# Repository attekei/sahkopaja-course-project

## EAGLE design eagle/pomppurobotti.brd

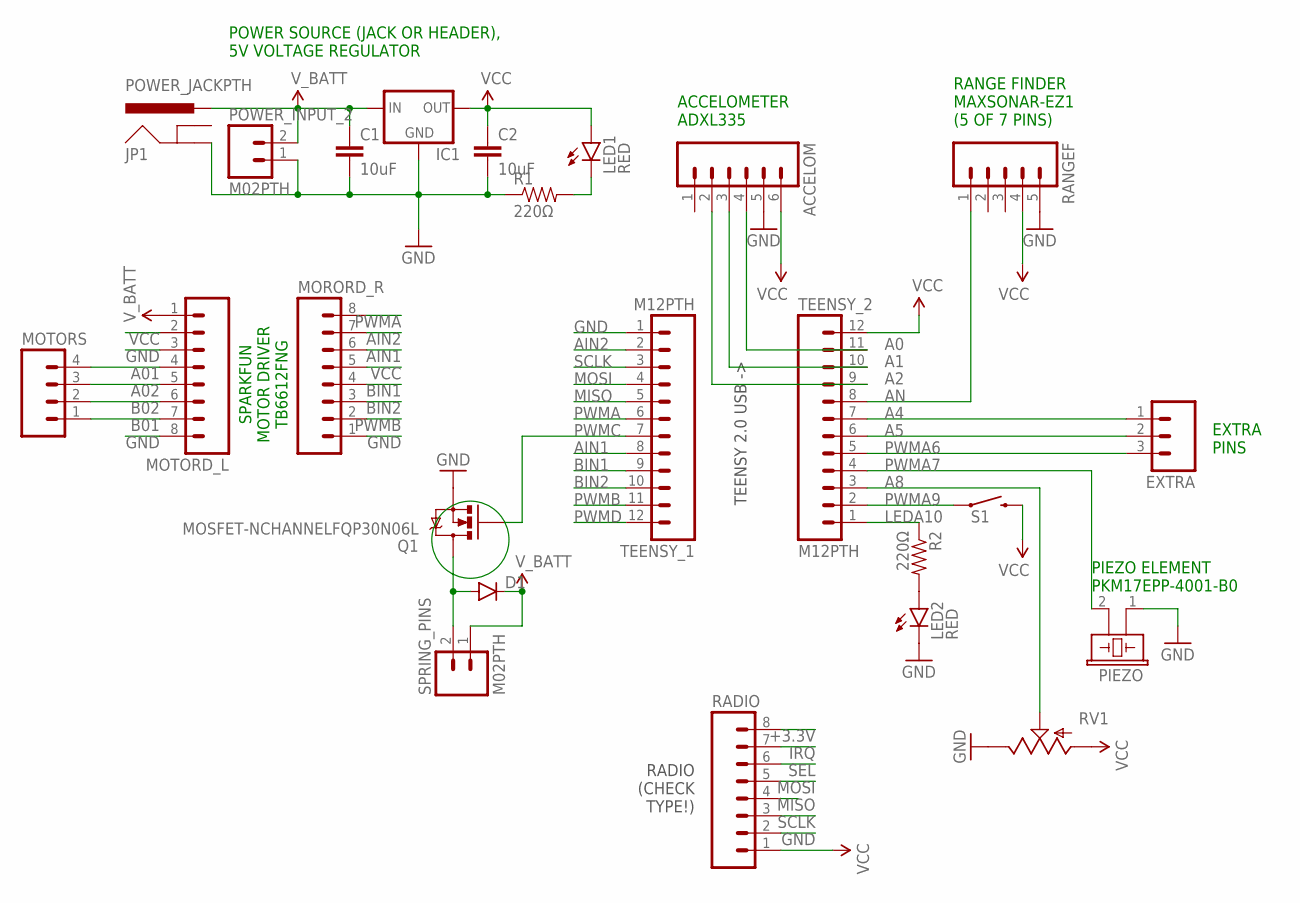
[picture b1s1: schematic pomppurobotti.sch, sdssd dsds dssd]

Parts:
ACCELOM: M06SILK_FEMALE_PTH; 1X06
C1, C2: 10uF; CAP-PTH-SMALL
D1: DIODEPTH; DIODE-1N4001
EXTRA: M03PTH; 1X03
IC1: V_REG_78XX-TO-220; TO-220-ALT
JP1: POWER_JACKPTH; POWER_JACK_PTH
LED1, LED2: RED; LED5MM
MORORD_R: M08LONGPADS; 1X08_LONGPADS
MOTORD_L: M08LONGPADS; 1X08_LONGPADS
MOTORS: M04PTH; 1X04
PIEZO: EFBAA40D101
POWER_INPUT_2: M02PTH; 1X02
Q1: MOSFET-NCHANNELFQP30N06L; TO220V
R1, R2: 220Ω; AXIAL-0.3
RADIO: M08; 1X08_ROUND
RANGEF: M05PTH; 1X05
RV1: POTTRIM; TRIM_POT
S1: SWITCH-MOMENTARY-2PTH; TACTILE-PTH
SPRING_PINS: M02PTH; 1X02
TEENSY_1, TEENSY_2: M12PTH; 1X12

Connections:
+3.3V: RADIO.8
A0: ACCELOM.2, TEENSY_2.9
A1: ACCELOM.3, TEENSY_2.10
A01: MOTORD_L.4, MOTORS.4
A2: ACCELOM.4, TEENSY_2.11
A02: MOTORD_L.5, MOTORS.3
A4: EXTRA.1, TEENSY_2.7
A5: EXTRA.2, TEENSY_2.6
A8: RV1.1 (S), TEENSY_2.3
AIN1: MORORD_R.6, TEENSY_1.8
AIN2: MORORD_R.7, TEENSY_1.2
AN: RANGEF.1, TEENSY_2.8
B01: MOTORD_L.7, MOTORS.1
B02: MOTORD_L.6, MOTORS.2
BIN1: MORORD_R.4, TEENSY_1.9
BIN2: MORORD_R.3, TEENSY_1.10
GND: ACCELOM.5, C1.2, C2.2, IC1.GND, JP1.GND, LED2.K (C), MORORD_R.1, MOTORD_L.3, MOTORD_L.8, PIEZO.1, POWER_INPUT_2.1, Q1.3 (S), R1.P$1 (1), RADIO.2, RANGEF.5, RV1.2 (E), TEENSY_1.1
IRQ: RADIO.7
LEDA10: R2.P$1 (1), TEENSY_2.1
MISO: RADIO.4, TEENSY_1.5
MOSI: RADIO.5, TEENSY_1.4
unnamed: LED1.K (C), R1.P$2 (2)
unnamed: LED2.A, R2.P$2 (2)
unnamed: D1.A, Q1.2 (D), SPRING_PINS.2
PWMA: MORORD_R.8, TEENSY_1.6
PWMA6: EXTRA.3, TEENSY_2.5
PWMA7: PIEZO.2, TEENSY_2.4
PWMA9: S1.1, TEENSY_2.2
PWMB: MORORD_R.2, TEENSY_1.11
PWMC: Q1.1 (G), TEENSY_1.7
PWMD: TEENSY_1.12
SCLK: RADIO.3, TEENSY_1.3
SEL: RADIO.6
VCC: ACCELOM.6, C2.1, IC1.OUT, LED1.A, MORORD_R.5, MOTORD_L.2, RADIO.1, RANGEF.4, RV1.3 (A), S1.3 (2), TEENSY_2.12
V_BATT: C1.1, D1.C, IC1.IN, JP1.PWR, MOTORD_L.1, POWER_INPUT_2.2, SPRING_PINS.1

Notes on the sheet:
TEENSY 2.0 USB ->
RADIO (CHECK TYPE!)
SPARKFUN MOTOR DRIVER TB6612FNG
ACCELOMETER ADXL335
POWER SOURCE (JACK OR HEADER), 5V VOLTAGE REGULATOR
PIEZO ELEMENT PKM17EPP-4001-B0
RANGE FINDER MAXSONAR-EZ1 (5 OF 7 PINS)
EXTRA PINS

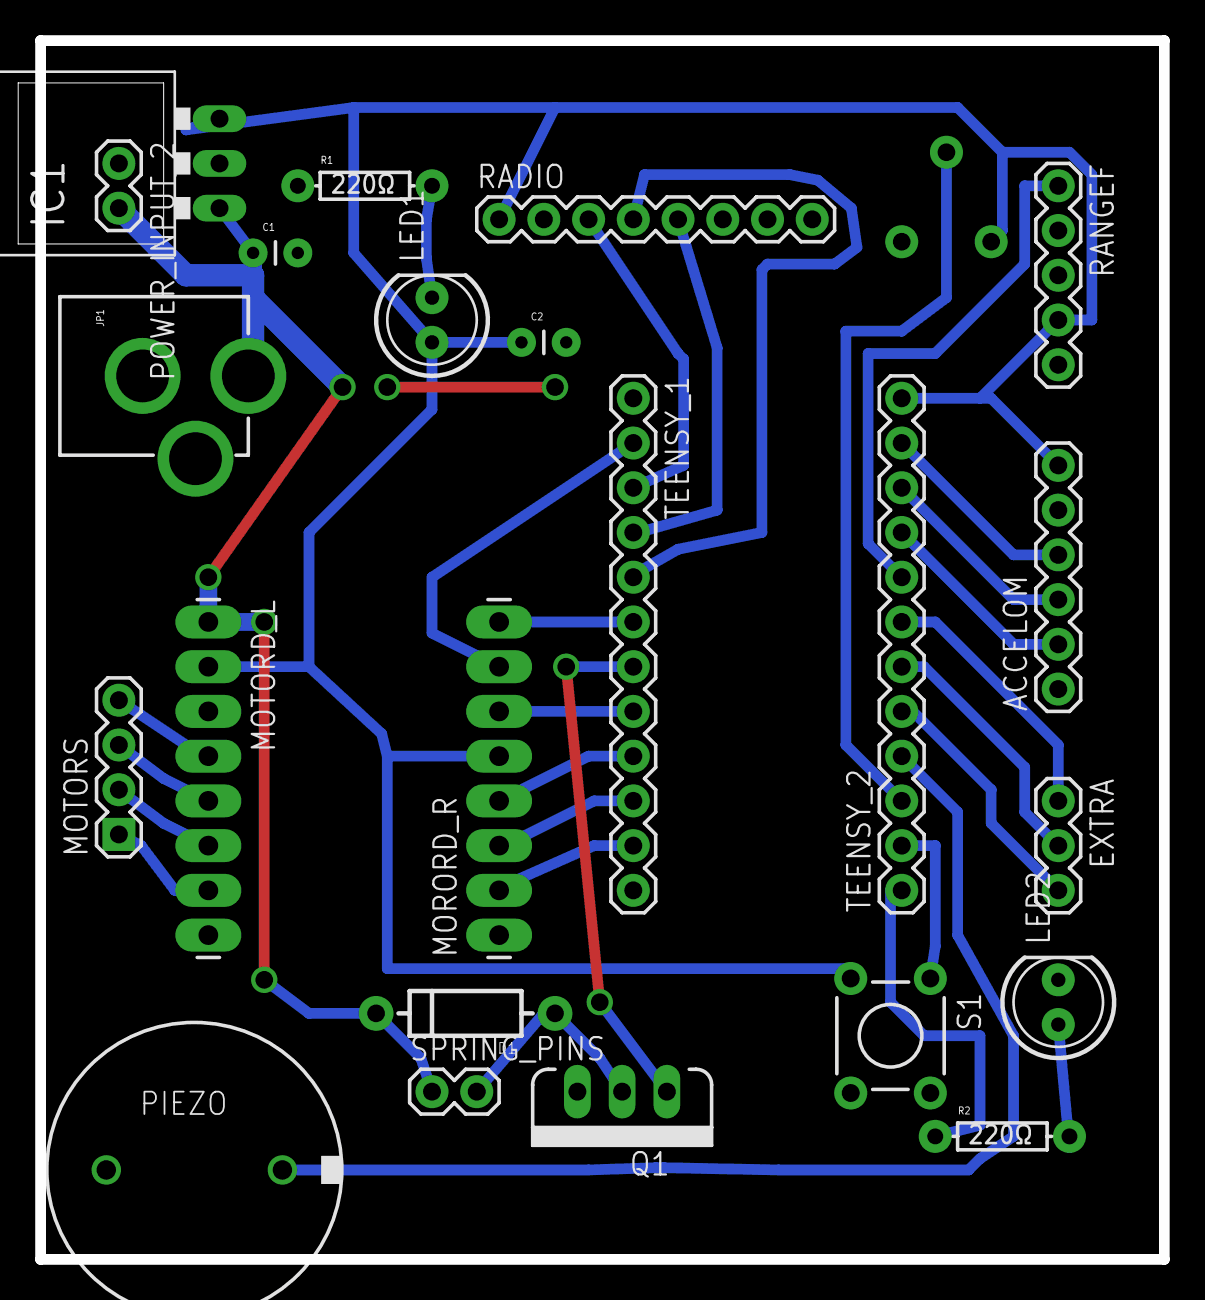
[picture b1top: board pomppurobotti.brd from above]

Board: 2 copper layers, 63.8 x 69.2 mm, 24 parts (0 on the bottom side), 31 nets.

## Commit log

2014-11-06 Update cylinder. Add ready-to-print model for Ultimaker.
2014-11-12 Move scad files to own folder
2014-11-12 Add initial eagle files
2014-11-12 Updates to schemantic and board files
2014-11-21 Update eagle files
2014-11-22 First version of PCB
2014-11-22 Remove backup files from git
2014-11-22 Add author info to schematic, add preview images
2014-11-23 Many major improvements
2014-11-23 Fix to proximity sensor position etc
2014-11-24 Update the board to use voltage regulator only for Teensy and sensors
2014-12-11 Add Arduino tests and modified RF library. Update Eagle schematics.
2015-02-23 Add new spring trigger scad file and ready-to-use model
2015-02-23 Update hole radius
2015-02-23 Increase spring scale
2015-02-23 Add basis for spring-containing component
2015-03-04 Get rid of hard-coded numbers in spring SCAD
2015-03-04 Valmiit polkyt, joiden sisaan pomppumekanismin varret menevat ja tiedosto, johon tulee varren malli
2015-03-04 Add holes to spring. Add STL model of spring.
2015-03-04 Add visual memories from the project
2015-03-09 Varsi updated
2015-03-09 Tune spring component
2015-03-09 Add STL models for 3d printer
2015-03-11 The whole model is now problem. Hopefully the size of the hole is now ok too.
2015-03-11 A typo in the previous command message. The whole model is now bigger. Hopefully the size of the hole is now ok too.
2015-04-13 Increase radius
2015-04-13 Add STL
2015-04-13 Unify hole radiuses
2015-04-13 Don't have a hole in spring trigger model, better to do it later with a drill
2015-04-13 Add missing STL files
2015-04-13 Another radius fix. I love 3d printing :heart_eyes:
2015-04-15 Mekanismipolkyt is now ready and suitable to the new bar.
2015-04-15 Update spring component dimensions for new bar
2015-04-15 Update spring component STL
2015-04-15 Some more strength to trigger :punch:
2015-04-15 Fix spring component. Add WIP assembled mechanism.
2015-04-15 Screw code was accidentally left out, ugh.
2015-04-15 A new folder for remote control
2015-04-15 Add animated assembled mechanism & video.
2015-04-16 Final improvements to spring trigger

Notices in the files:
parts and their libraries:
SparkFun-Connectors: Licensing: Creative Commons ShareAlike 4.0 International - https://creativecommons.org/licenses/by-sa/4.0
